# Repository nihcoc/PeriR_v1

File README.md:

# PeriR

A custom Software Defined Radio (SDR) carrier board built around the **Xilinx Zynq-7020 SoC** and **Analog Devices AD9364** RF transceiver. The board is designed to run **Kuiper Linux** (Analog Devices' Raspberry Pi OS-based distro) out of the box, with native support for GNU Radio and SDR++ applications.

---

## Overview

This project is inspired by the [FreeSRP](http://electronics.kitchen/misc/freesrp/) open-source SDR by Lukas Lao Beyer and borrows design references from the **FMCOMMS4**, **Zedboard**, **ADRV9364-Z7020**, and **PlutoSDR**.

The goal is a powerful, Linux-capable SDR transceiver with a compact form factor and eventually, a handheld device like the HackRF Portapack.

---

## Key Specifications

| Feature | Detail |
|---|---|
| **SoC / FPGA** | Xilinx Zynq-7020 (ARM Cortex-A9, ~85K LUTs) |
| **RF Transceiver** | Analog Devices AD9364 |
| **Frequency Range** | 70 MHz – 6.0 GHz |
| **Bandwidth** | 200 kHz – 56 MHz |
| **RAM** | 2× 128MB DDR3 (256MB total, Zedboard config) |
| **OS** | Kuiper Linux (Analog Devices / Raspberry Pi OS based) |
| **Primary Storage** | MicroSD card |

---

## Block Diagram

```
Antenna
   │
   ▼
AD9364 RF Transceiver (70MHz–6GHz)
   │  LVDS (max throughput)
   ▼
Zynq-7020 (PS + PL)
   ├── ARM Cortex-A9 (PS) ──► DDR3 RAM, SD Card, USB-OTG, Ethernet, HDMI
```

---

## Hardware Design

### RF Transceiver — AD9364
- **Signalling standard:** LVDS (chosen over CMOS for lower EMI and higher throughput)
- **Interface:** Connected to FPGA Bank 34 (VCCO = 2.5V, `LVDS_25` standard)
- **Balun:** TCM1-63AX+ wideband RF transformer (≤1.8 dB insertion loss @ 6 GHz)
- **Clock:** 40 MHz, 10 pF load capacitance (tested reference from AD)
- **Power rail:** 1.3V via ADP1754ACPZ-1.3-R7 (AD-recommended for stability)
- **TX Power Amp:** PGA-102 (dedicated clean 3.3V supply)

### Zynq-7020 SoC
- **PS Clock:** 33.33 MHz  
- **PL Clock:** 100 MHz (EPSON SG-8018CA oscillator)
- **Boot:** SD Card (primary), QSPI Flash (fallback)
- **Configuration:** Boot mode selectable via header pins/switches
- **RAM interface:** Signal lines terminated at 40 Ω

### Power Architecture

Power sequencing follows **DS187** requirements:
1. VCCPINT (1.0V)
2. VCCPAUX + VCCPLL (1.8V) — simultaneously
3. PS VCCO supplies: VCCOMIO0, VCCOMIO1, VCCO_DDR (3.3V / 1.5V / 0.75V)

| Rail | IC | Current | Usage |
|---|---|---|---|
| 1.0V | TPS62130A | 3A | Zynq VCCINT, VCCBRAM |
| 1.8V | TPS62130A | 3A | Zynq VCCAUX, VCCADC, MIO logic |
| 3.3V | TPS65251-3RHAR (Ch1) | 3A | I/O, SD card, interfaces |
| 2.5V | TPS65251-3RHAR (Ch2) | 2A | FPGA Bank 34 (LVDS) |
| 1.5V | TPS65251-3RHAR (Ch3) | 2A | DDR3 VCCIO |
| 0.75V | MAX1510ETB+ | — | DDR3 VTT termination |
| 1.3V | ADP1754ACPZ-1.3-R7 | — | AD9364 primary supply |
| 5V | External connector | — | Board input power |

> Sequencing is managed using EN (Enable) and PG (Power Good) pins chained between power ICs.
> AD7291BCPZ added for full-board power monitoring.

### Interfaces

| Interface | IC / Notes |
|---|---|
| **HDMI** | ADV7511 transmitter — follows Zedboard design for Kuiper Linux compatibility |
| **USB-OTG** | Standard USB 2.0 OTG with ESD protection |
| **Ethernet** | GbE — backup interface for setup and testing |
| **SD Card** | Level-shifted (1.8V MIO → 3.3V SD logic) |
| **QSPI Flash** | MT25QU128ABA — 128Mb, all data lines active |

## Software

- **OS:** [Kuiper Linux](https://wiki.analog.com/resources/tools-software/linux-software/kuiper-linux) by Analog Devices
- **SDR Applications:** GNU Radio, SDR++
- **FPGA toolchain:** Xilinx Vivado + Analog Devices HDL reference designs
- **Reference HDL:** [Analog Devices HDL](https://github.com/analogdevicesinc/hdl) (FMCOMMS4 / ADRV9364 compatible)

---

## Design References

- [FreeSRP](http://electronics.kitchen/misc/freesrp/) — Lukas Lao Beyer
- Analog Devices FMCOMMS4
- Xilinx Zedboard
- ADRV9364-Z7020
- PlutoSDR
- **Key Datasheets:** UG585, UG933, UG482, UG470, UG483, DS187, AD9364 Reference Manual

---

## Project Status

- [x] Component selection
- [x] Schematic capture
- [x] Footprint assignment
- [x] Schematic verification (round 1)
- [ ] Schematic verification (round 2)
- [ ] PCB layout & routing
- [ ] DFM review
- [ ] Fabrication & assembly
- [ ] Bring-up & firmware development
- [ ] HAT board design

---

*This is a personal learning project. Feedback and suggestions welcome — especially on the RF and LVDS sections!*

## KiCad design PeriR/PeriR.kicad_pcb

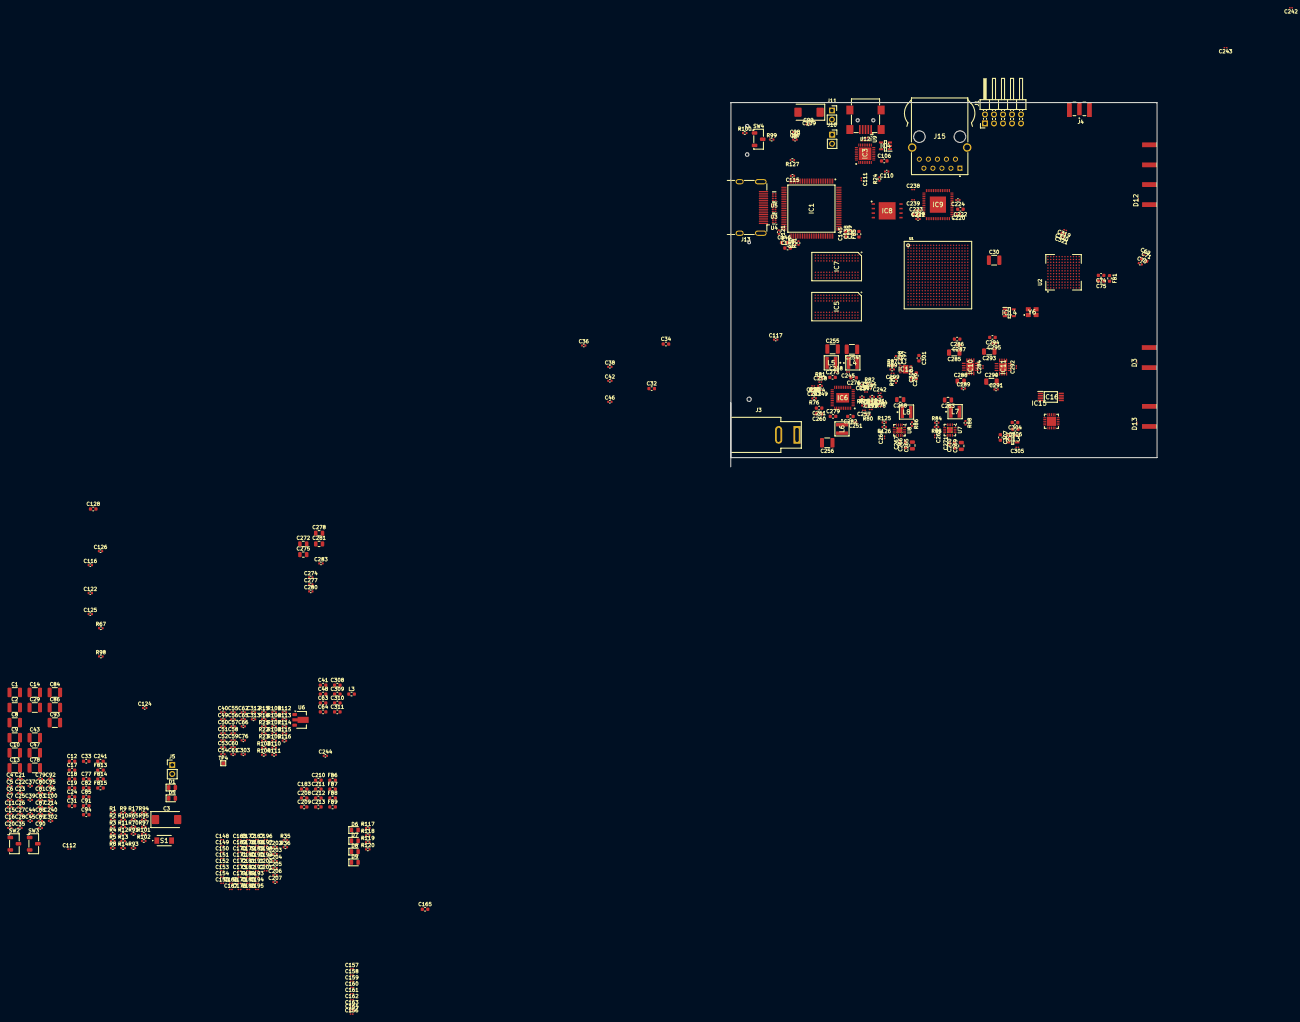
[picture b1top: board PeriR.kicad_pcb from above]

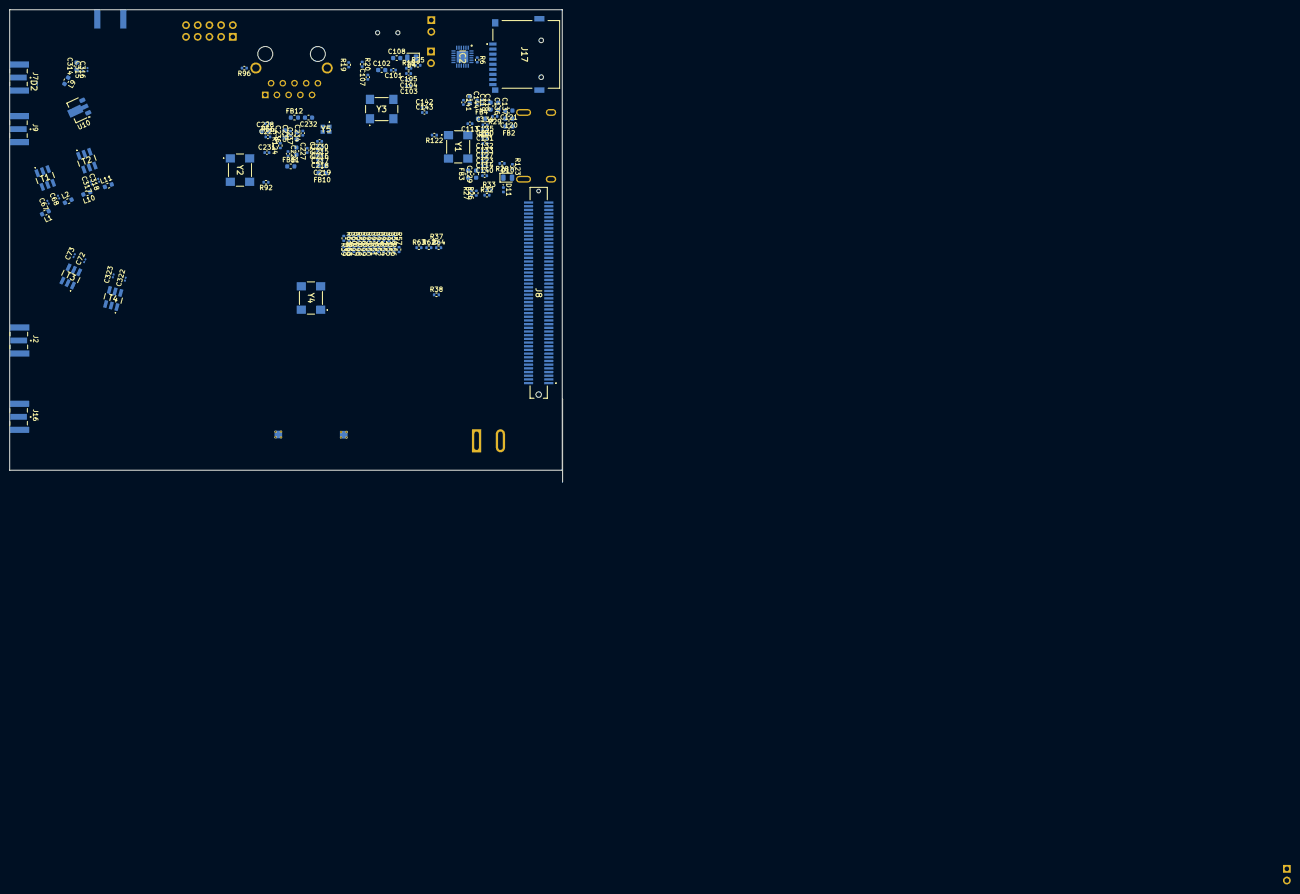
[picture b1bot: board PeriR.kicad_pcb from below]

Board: 6 copper layers, 120.1 x 102.6 mm, 546 parts (135 on the bottom side), 420 nets, no tracks yet.

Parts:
C1, C2: 4.7uF; C_1210_3225Metric
C3: 330uF; CP_EIA-7343-31_Kemet-D
C4, C5, C6, C7, C11, C15, C16, C20, C21, C22, C23, C25, C26, C27, C28, C35, C36, C37, C38, C39, C42, C45, C46, C79, C80, C81, C83, C87, C88, C89, C90, C92, C95, C240, C302: 0.47uF; C_0402_1005Metric
C8, C9, C13, C29, C30, C47, C78, C84, C86, C93: 100uF; C_1210_3225Metric
C10, C14, C43: 47uF; C_1210_3225Metric
C12, C17, C18, C19, C24, C31, C32, C33, C34, C77, C82, C85, C91, C94, C108, C165, C183, C219, C222, C228, C232, C237, C308: 4.7uF; C_0603_1608Metric
C40, C44, C49, C50, C51, C52, C53, C54, C55, C56, C57, C58, C59, C60, C61, C62, C65, C66, C96, C97, C98, C99, C100, C101, C103, C104, C105, C107, C110, C113, C114, C115, C116, C117, C118, C119, C122, C123, C124, C125, C126, C127, C130, C131, C132, C133, C134, C135, C138, C139, C140, C141, C142, C143, C202, C203, C204, C205, C206, C207, C214, C215, C216, C217, C218, C220, C221, C224, C225, C226, C229, C230, C231, C233, C234, C235, C303, C312, C313: 0.1uF; C_0402_1005Metric
C41, C48, C120, C128, C136, C144, C146, C147, C210, C211, C223, C227, C236, C300, C304, C306, C307, C309, C314: 1uF; C_0603_1608Metric
C63, C64, C71, C74, C75, C121, C129, C137, C145, C261, C266, C270, C273, C276, C279, C282, C286, C294, C301, C310, C311: 10uF; C_0603_1608Metric
C67, C68, C72, C73, C317, C318, C322, C323: 18pF; C_0201_0603Metric
C69, C299, C319: 1nF; C_0201_0603Metric
C70, C267, C271, C274, C277, C280, C283, C287, C289, C291, C295, C297, C320: 100nF; C_0402_1005Metric
C76: 0.1uF (DNP); C_0402_1005Metric
C102, C106: 22uF; C_0603_1608Metric
C109: 150uF; CP_EIA-7343-31_Kemet-D
C111: 15pF; C_0201_0603Metric
C112, C184, C185, C186, C187, C196, C197, C198, C199, C200, C201, C284, C292, C305: 10nF; C_0201_0603Metric
C148, C149, C150, C151, C152, C153, C154, C155, C156, C157, C158, C159, C160, C161, C162, C163, C166, C167, C168, C169, C170, C171, C172, C173, C174, C175, C176, C177, C178, C179, C180, C181, C188, C189, C190, C191, C192, C193, C194, C195, C245, C248, C251: 47nF; C_0201_0603Metric
C164: 470nF; C_0402_1005Metric
C182: 470nF; C_0201_0603Metric
C208, C209: 10nF; C_0603_1608Metric
C212, C213: 2.2uF; C_0603_1608Metric
C238, C239: 39pF; C_0201_0603Metric
C241: 10uF(0603); C_0603_1608Metric
C242, C316: 68pF; C_0201_0603Metric
C242#2, C243, C244#2, C246, C250, C253, C257, C258, C259: 4.7nF; C_0201_0603Metric
C243#2, C315: 1.2nF; C_0201_0603Metric
C244: 1uF; C_0402_1005Metric
C247, C249, C252: 100pF; C_0201_0603Metric
C254, C255, C256: 22uF; C_1210_3225Metric
C260: 3.3uF; C_0603_1608Metric
C262, C264: 2.2nF; C_0201_0603Metric
C263, C268: 22uF; C_0805_2012Metric
C265, C269, C272, C275, C278, C281, C288: 47uF; C_0805_2012Metric
C285, C290, C293: 47uF; C_1206_3216Metric
C296: 100uF; C_0402_1005Metric
C298: 0.33uF; C_0402_1005Metric
C321: 10uF; C_0201_0603Metric
D1, D6, D7, D8, D9: LED; LED_0805_2012Metric
D2, D3, D12, D13: ESD8472MUT5G; X3DFN2-CASE152AF-ISSUE-A
D4: D; D_0805_2012Metric
D5, D10: D_Schottky; D_0805_2012Metric
D11: PESD0402-140; D_0402_1005Metric
FB1, FB2, FB3, FB4, FB5, FB6, FB7, FB8, FB9: BLM21AG601SN1D; L_0603_1608Metric
FB10, FB11, FB12: MPZ1608S101ATAH0; L_0603_1608Metric
FB13: BLM18SG121TN1D; L_0603_1608Metric
FB14, FB15: BLM18SG221TN1D; L_0603_1608Metric
IC1: ADV7511KSTZ; QFP50P1600X1600X160-100N
IC2: TXS02612RTWR; QFN50P400X400X80-25N-D
IC3: TUSB1210BRHB; QFN50P500X500X100-33N-D
IC4: TPS2051BDBVTG4; SOT95P280X145-5N
IC5, IC7: MT41K128M16JT-125 :K; BGA96C80P9X16_800X1400X120
IC6: TPS65251-3RHAR; QFN50P600X600X100-41N-D
IC8: S25FL256SAGNFI001; SON127P800X600X80-9N-D
IC9: 88E1512-XX-NNP2I000; QFN50P800X800X100-57N-D
IC10, IC11: ADP1754ACPZ-1.3-R7; QFN65P400X400X80-17N-D
IC12: MAX1510ETB+; SON50P300X300X80-11N
IC13: NCP700BSN33T1G; SOT95P275X110-5N
IC14: ADM7160AUJZ-1.8-R7; SOT95P280X100-5N
IC15: AD7291BCPZ; QFN50P400X400X80-21N
IC16: M24C02-WDW6TP; SOP65P640X120-8N
J1: Conn_02x05_Top_Bottom; PinHeader_2x05_P2.54mm_Horizontal
J2, J4, J7, J9, J16: SMA-J-P-H-ST-EM1; SAMTEC_SMA-J-P-H-ST-EM1
J3: Barrel_Jack; BarrelJack_SwitchcraftConxall_RAPC10U_Horizontal
J5: Conn_01x02_Pin; PinHeader_1x02_P2.54mm_Vertical
J8: 61082-101400LF; 61082101400LF
J10, J11: Conn_01x02_Pin; PinSocket_1x02_P2.54mm_Vertical
J12: USB_B_Mini; USB_Mini-B_Wuerth_65100516121_Horizontal
J13: HDMI_A_1.4; HDMI_A_Molex_208658-1001_Horizontal
J15: HFJ11-1G02ERL; HFJ111G02ERL
J17: MICRO-SD-CARD; MICROSDCARD
L1, L2, L10, L11: 330LH; L_0603_1608Metric
L3, L9: 43nH; L_0603_1608Metric
L4: 1uH; XFL4020-222ME
L5, L6: 1.5uH; XFL4020-222ME
L7, L8: 2.2uH; XFL4020-222ME
R1, R3, R6, R24, R64, R122, R124: 4.7K; R_0402_1005Metric
R2: 270R; R_0402_1005Metric
R4, R15, R34, R87, R89, R90, R102, R103, R105, R107, R109, R111, R113, R115: 10K; R_0402_1005Metric
R5, R7, R17: 4.7K(0R); R_0402_1005Metric
R8, R9, R10, R11, R12, R13, R14, R73, R74, R77: 20K; R_0402_1005Metric
R16: 14.3K 1%; R_0402_1005Metric
R18, R26, R27, R28, R30, R31: 2K; R_0402_1005Metric
R19, R20, R86, R88: 100K; R_0402_1005Metric
R21, R22: 1R; R_0402_1005Metric
R23, R67, R97: 49.9R; R_0402_1005Metric
R25, R66, R96: 0R; R_0402_1005Metric
R29: 887R; R_0402_1005Metric
R32, R33: 50R; R_0402_1005Metric
R35, R36, R62: 80R; R_0402_1005Metric
R37, R38: 240R; R_0402_1005Metric
R39, R40, R41, R42, R43, R44, R45, R46, R47, R48, R49, R50, R51, R52, R53, R54, R55, R56, R57, R58, R59, R60, R61, R63: 40R; R_0402_1005Metric
R65, R117, R118, R119, R120: 330R; R_0402_1005Metric
R70: 100k; R_0402_1005Metric
R71, R75, R78: 40.2K; R_0402_1005Metric
R72: 12.8K; R_0402_1005Metric
R76: 45.9K; R_0402_1005Metric
R79: 18.9K; R_0402_1005Metric
R80, R81: 137K; R_0402_1005Metric
R82: 86.6K; R_0402_1005Metric
R83: 135.4K; R_0402_1005Metric
R84: 51K; R_0402_1005Metric
R85, R125: 200K; R_0402_1005Metric
R91, R92: 24R; R_0402_1005Metric
R93, R94, R95: 10k; R_0402_1005Metric
R98, R127: 499R; R_0402_1005Metric
R99, R100: 50K; R_0402_1005Metric
R101: 1K; R_0402_1005Metric
R104, R106, R108, R110, R112, R114, R116: 16K; R_0402_1005Metric
R121: 50; R_0402_1005Metric
R123: 27K; R_0402_1005Metric
R126: 160K; R_0402_1005Metric
S1: TS-1088-AR02016; TS1088AR02016
SW2, SW3, SW4: SW_Nidec_CAS-120A1; Nidec_Copal_CAS-120A
T1, T2, T3, T4: TCM1-63AX_; TCM163AX
TP4: TestPoint; TestPoint_Pad_1.0x1.0mm
U1: XC7Z020CLG484; CS484
U2: AD9364BBCZ; BGA144C80P12X12_1000X1000X170N
U3, U4, U5, U9: TPD4E05U06DQA; USON-10_2.5x1.0mm_P0.5mm
U6, U10: PGA-102; SOT-89-3
U7, U8: TPS62130A; VQFN-16-1EP_3x3mm_P0.5mm_EP1.68x1.68mm_ThermalVias
Y1: XL2EL89COI-111YLC-12M; SG8018CA1000000MTJHSA0
Y2: OT3EL89CJI-111YLC-33.33M; SG8018CA1000000MTJHSA0
Y3: XL2EL89COI-111YLC-26M; SG8018CA1000000MTJHSA0
Y4: SG-8018CA_100.0000M-TJHSA0; SG8018CA1000000MTJHSA0
Y5: NX2016SA-25MHZ-STD-CZS-2; FA128400000MF20XK
Y6: ECS-TXO-32CSMV-400-BN-TR; ECSTXO32CSMV400BNTR

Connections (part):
0V75: C202.1, C203.1, C204.1, C205.1, C206.1, C207.1, C208.1, C209.1, C210.1, C211.1, C212.1, C213.1, C296.1, IC12.6 (OUTS), IC12.9 (OUT), R39.2, R40.2, R41.2, R42.2, R43.2, R44.2, R45.2, R46.2, R47.2, R48.2, R49.2, R50.2, R51.2, R52.2, R53.2, R54.2, R55.2, R56.2, R57.2, R58.2, R59.2, R60.2, R61.2, R63.1
1V0_PG: R88.2, U7.4 (PG), U7.7 (FSW), U8.13 (EN)
1V3_PG: IC10.5 (PG), IC11.5 (PG)
1V8_PG: IC6.11 (EN1), IC6.20 (EN2), IC6.40 (EN3), R86.2, U8.4 (PG), U8.7 (FSW)
+1V0: C1.1, C2.1, C3.1, C4.1, C5.1, C6.1, C7.1, C8.1, C10.1, C11.1, C47.1, C77.1, C79.1, C80.1, C81.1, C263.1, L7.2, R84.1, R88.1, R111.1, U1.G8 (VCCPINT@0), U1.H9 (VCCPINT@1), U1.H11 (VCCBRAM@0), U1.J8 (VCCPINT@2), U1.J10 (VCCBRAM@1), U1.J12 (VCCINT@0), U1.J14 (VCCINT@1), U1.K13 (VCCINT@2), U1.L8 (VCCPINT@3), U1.L14 (VCCINT@3), U1.M13 (VCCINT@4), U1.N8 (VCCPINT@4), U1.N14 (VCCINT@5), U1.P13 (VCCINT@6), U1.R8 (VCCPINT@5), U1.R14 (VCCINT@7), U7.14 (VOS)
+1V3: C49.1, C50.1, C51.1, C52.1, C53.1, C54.1, C55.1, C56.1, C57.1, C75.1, C293.1, C294.1, C295.1, FB1.2, IC11.9 (SENSE), IC11.10 (VOUT_1), IC11.11 (VOUT_2), IC11.12 (VOUT_3), IC11.13 (VOUT_4), IC11.14 (VOUT_5), R109.1, U2.A7 (VDDA1P3_RX_TX), U2.A8 (VDDA1P3_RX_TX), U2.A9 (VDDA1P3_RX_TX), U2.A10 (VDDA1P3_RX_TX), U2.D2 (VDDA1P3_RX_RF), U2.D3 (VDDA1P3_RX_TX), U2.E3 (VDDA1P3_TX_LO_BUFFER), U2.F12 (VDDD1P3_DIG), U2.K4 (VDDA1P3_BB)
+1V3SYNTH: C58.1, C59.1, C60.1, C61.1, C62.1, C63.1, C64.1, C285.1, C286.1, C287.1, IC10.9 (SENSE), IC10.10 (VOUT_1), IC10.11 (VOUT_2), IC10.12 (VOUT_3), IC10.13 (VOUT_4), IC10.14 (VOUT_5), U2.B9 (VDDA1P3_TX_LO), U2.B10 (VDDA1P3_TX_VCO_LDO), U2.E2 (VDDA1P3_RX_LO), U2.F2 (VDDA1P3_RX_VCO_LDO), U2.J3 (VDDA1P3_RX_SYNTH), U2.K3 (VDDA1P3_TX_SYNTH)
+1V3_TX: C69.1, C70.1, C71.1, C74.1, C319.1, C320.1, C321.1, FB1.1, L1.2, L2.2, L10.2, L11.2
+1V5: C84.1, C85.1, C87.1, C88.1, C89.1, C90.1, C148.1, C149.1, C150.1, C151.1, C152.1, C153.1, C154.1, C155.1, C156.1, C157.1, C158.1, C159.1, C160.1, C161.1, C162.1, C163.1, C164.1, C165.1, C166.1, C167.1, C168.1, C169.1, C170.1, C171.1, C172.1, C173.1, C174.1, C175.1, C176.1, C177.1, C178.1, C179.1, C180.1, C181.1, C182.1, C183.1, C184.1, C188.1, C189.1, C190.1, C191.1, C192.1, C193.1, C194.1, C195.1, C196.1, C197.1, C198.1, C199.1, C200.1, C202.2, C203.2, C204.2, C205.2, C206.2, C207.2, C208.2, C209.2, C210.2, C211.2, C212.2, C213.2, C243.2, C255.1, FB6.1, FB6.2, FB7.1, FB7.2, FB8.1, FB8.2, FB9.1, FB9.2, IC5.A1 (VDDQ_1), IC5.A8 (VDDQ_2)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
+1V8: C12.1, C14.1, C15.1, C16.1, C44.1, C78.1, C82.1, C83.1, C93.1, C94.1, C95.1, C99.2, C103.2, C104.2, C105.2, C268.1, C288.2, C289.2, C290.2, C291.2, FB2.1, FB4.1, FB5.1, FB11.1, FB13.1, FB14.2, IC2.5 (VCCA), IC3.11 (CS), IC3.14 (CFG), IC3.28 (VDD18_1), IC3.30 (VDD18_2), IC3.32 (VDDIO), IC10.1 (VIN_1), IC10.2 (VIN_2), IC10.3 (VIN_3), IC10.4 (EN), IC10.15 (VIN_4), IC10.16 (VIN_5), IC11.1 (VIN_1), IC11.2 (VIN_2), IC11.3 (VIN_3), IC11.4 (EN), IC11.15 (VIN_4), IC11.16 (VIN_5), J8.91, J8.93, J8.95, J8.97, J8.99, L8.2, R18.2, R70.2, R86.1, R93.2, R94.2, R99.2, R113.1, R124.1, R125.1, U1.A10 (VCCO_MIO1_501@0), U1.B13 (VCCO_MIO1_501@1), U1.D9 (VCCO_MIO1_501@2), U1.E12 (VCCO_MIO1_501@3), U1.G9 (VCCBATT_0), U1.K9 (VCCPAUX@0), U1.L10 (VCCAUX@0), U1.M9 (VCCPAUX@1), U1.N10 (VCCAUX@1), U1.P9 (VCCPAUX@2), U1.P11 (VCCAUX@2), U1.R10 (VCCAUX@3), U1.T9 (VCCPAUX@3), U8.14 (VOS)
+2V5: C9.1, C13.1, C17.1, C18.1, C19.1, C20.1, C21.1, C22.1, C23.1, C24.1, C25.1, C26.1, C27.1, C28.1, C66.1, C244#2.2, C256.1, L6.2, R15.1, R19.1, R78.1, R102.2, R115.1, U1.A20 (VCCO_35@0), U1.C16 (VCCO_35@1), U1.D19 (VCCO_35@2), U1.E22 (VCCO_35@3), U1.F15 (VCCO_35@4), U1.G18 (VCCO_35@5), U1.H21 (VCCO_35@6), U1.K17 (VCCO_34@0), U1.L20 (VCCO_34@1), U1.N16 (VCCO_34@2), U1.P19 (VCCO_34@3), U1.R22 (VCCO_34@4), U1.T15 (VCCO_34@5), U2.H12 (VDD_INTERFACE)
+3V3: C29.1, C30.1, C31.1, C32.1, C33.1, C34.1, C35.1, C36.1, C37.1, C38.1, C39.1, C42.1, C43.1, C45.1, C46.1, C65.1, C86.1, C91.1, C92.1, C96.1, C97.2, C98.2, C100.1, C101.2, C102.2, C110.2, C113.2, C214.2, C242#2.2, C254.1, C300.2, C301.2, C311.2, C312.2, C313.2, FB3.1, FB10.1, FB12.1, IC2.21 (VCCB0), IC3.20 (VDD33), IC8.8 (VCC), IC12.2 (VCC), IC12.7 (~SHDN), IC12.10 (IN), IC14.1 (VIN), IC14.3 (EN), IC15.10 (VDD), IC15.16 (VDRIVE), IC15.17 (~PD/~RST), IC16.8 (VCC), J1.2, J8.41, J8.43, J8.45, J8.47, J8.49, J15.9 (VCC), J17.4 (VDD), L4.2, R1.1, R2.1, R3.1, R4.2, R5.1, R6.1, R14.2, R17.1, R24.2, R26.1, R27.1, R28.1, R65.1, R71.1, R90.1, R103.1, R122.2, R123.1, SW2.3 (A), SW3.3 (A), U1.AA10 (VCCO_13@5)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
+3V3_TX: C242.1, C243#2.1, C244.1, C304.1, C306.1, C314.1, C315.1, C316.1, IC13.5 (OUT), L3.1, L9.1
+5V: C107.2, C265.2, C266.2, C267.2, C269.2, C270.2, C271.2, C272.1, C273.2, C274.2, C275.1, C276.2, C277.2, C278.1, C279.2, C280.2, C281.1, C282.2, C283.2, C307.1, IC4.5 (IN), IC6.13 (VIN1), IC6.18 (VIN2), IC6.32 (VIN_1), IC6.33 (VIN_2), IC6.34 (VIN_3), IC6.38 (VIN3), IC13.1 (IN), IC13.3 (EN), J3.1, J8.17, J8.19, J8.21, J8.23, J8.25, J8.27, J8.29, J8.31, J8.33, J8.35, J8.37, J8.39, J13.18 (+5V), R30.1, R31.1, U7.10 (VIN), U7.11 (VIN), U7.12 (VIN), U7.13 (EN), U8.10 (VIN), U8.11 (VIN), U8.12 (VIN)
/DDR/A0: IC5.N3 (A0), IC7.N3 (A0), R39.1, U1.M4 (PS_DDR_A0_502)
/DDR/A1: IC5.P7 (A1), IC7.P7 (A1), R40.1, U1.M5 (PS_DDR_A1_502)
/DDR/A2: IC5.P3 (A2), IC7.P3 (A2), R41.1, U1.K4 (PS_DDR_A2_502)
/DDR/A3: IC5.N2 (A3), IC7.N2 (A3), R42.1, U1.L4 (PS_DDR_A3_502)
/DDR/A4: IC5.P8 (A4), IC7.P8 (A4), R43.1, U1.K6 (PS_DDR_A4_502)
/DDR/A5: IC5.P2 (A5), IC7.P2 (A5), R44.1, U1.K5 (PS_DDR_A5_502)
/DDR/A6: IC5.R8 (A6), IC7.R8 (A6), R45.1, U1.J7 (PS_DDR_A6_502)
/DDR/A7: IC5.R2 (A7), IC7.R2 (A7), R46.1, U1.J6 (PS_DDR_A7_502)
/DDR/A8: IC5.T8 (A8), IC7.T8 (A8), R47.1, U1.J5 (PS_DDR_A8_502)
/DDR/A9: IC5.R3 (A9), IC7.R3 (A9), R48.1, U1.H5 (PS_DDR_A9_502)
/DDR/A10: IC5.L7 (A10/AP), IC7.L7 (A10/AP), R49.1, U1.J3 (PS_DDR_A10_502)
/DDR/A11: IC5.R7 (A11), IC7.R7 (A11), R50.1, U1.G5 (PS_DDR_A11_502)
/DDR/A12: IC5.N7 (A12/BC#), IC7.N7 (A12/BC#), R51.1, U1.H4 (PS_DDR_A12_502)
/DDR/A13: IC5.T3 (A13), IC7.T3 (A13), R52.1, U1.F4 (PS_DDR_A13_502)
/DDR/A14: IC5.T7 (A14), IC7.T7 (A14), R53.1, U1.G4 (PS_DDR_A14_502)
/DDR/BA0: IC5.N8 (BA1), IC7.N8 (BA1), R54.1, U1.L7 (PS_DDR_BA0_502)
/DDR/BA1: IC5.M3 (BA2), IC7.M3 (BA2), R55.1, U1.L6 (PS_DDR_BA1_502)
/DDR/BA2: IC5.M2 (BA0), IC7.M2 (BA0), R56.1, U1.M6 (PS_DDR_BA2_502)
/DDR/CAS: IC5.K3 (CAS#), IC7.K3 (CAS#), R57.1, U1.P3 (PS_DDR_CAS_B_502)
/DDR/CKE: IC5.K9 (CKE), IC7.K9 (CKE), R63.2, U1.V3 (PS_DDR_CKE_502)
/DDR/CKN: IC5.K7 (CK#), IC7.K7 (CK#), R62.2, U1.N5 (PS_DDR_CKN_502)
/DDR/CKP: IC5.J7 (CK), IC7.J7 (CK), R62.1, U1.N4 (PS_DDR_CKP_502)
/DDR/CS: IC5.L2 (CS#), IC7.L2 (CS#), R60.1, U1.P6 (PS_DDR_CS_B_502)
/DDR/DM0: IC7.E7 (LDM), U1.B1 (PS_DDR_DM0_502)
/DDR/DM1: IC7.D3 (UDM), U1.H3 (PS_DDR_DM1_502)
/DDR/DM2: IC5.E7 (LDM), U1.P1 (PS_DDR_DM2_502)
/DDR/DM3: IC5.D3 (UDM), U1.AA2 (PS_DDR_DM3_502)
/DDR/DQ0: IC7.E3 (DQ0), U1.D1 (PS_DDR_DQ0_502)
/DDR/DQ1: IC7.F7 (DQ1), U1.C3 (PS_DDR_DQ1_502)
/DDR/DQ2: IC7.F2 (DQ2), U1.B2 (PS_DDR_DQ2_502)
/DDR/DQ3: IC7.F8 (DQ3), U1.D3 (PS_DDR_DQ3_502)
/DDR/DQ4: IC7.H3 (DQ4), U1.E3 (PS_DDR_DQ4_502)
/DDR/DQ5: IC7.H8 (DQ5), U1.E1 (PS_DDR_DQ5_502)
/DDR/DQ6: IC7.G2 (DQ6), U1.F2 (PS_DDR_DQ6_502)
/DDR/DQ7: IC7.H7 (DQ7), U1.F1 (PS_DDR_DQ7_502)
/DDR/DQ8: IC7.D7 (DQ8), U1.G2 (PS_DDR_DQ8_502)
/DDR/DQ9: IC7.C3 (DQ9), U1.G1 (PS_DDR_DQ9_502)
/DDR/DQ10: IC7.C8 (DQ10), U1.L1 (PS_DDR_DQ10_502)
/DDR/DQ11: IC7.C2 (DQ11), U1.L2 (PS_DDR_DQ11_502)
/DDR/DQ12: IC7.A7 (DQ12), U1.L3 (PS_DDR_DQ12_502)
/DDR/DQ13: IC7.A2 (DQ13), U1.K1 (PS_DDR_DQ13_502)
/DDR/DQ14: IC7.B8 (DQ14), U1.J1 (PS_DDR_DQ14_502)
/DDR/DQ15: IC7.A3 (DQ15), U1.K3 (PS_DDR_DQ15_502)
/DDR/DQ16: IC5.E3 (DQ0), U1.M1 (PS_DDR_DQ16_502)
/DDR/DQ17: IC5.F7 (DQ1), U1.T3 (PS_DDR_DQ17_502)
/DDR/DQ18: IC5.F2 (DQ2), U1.N3 (PS_DDR_DQ18_502)
/DDR/DQ19: IC5.F8 (DQ3), U1.T1 (PS_DDR_DQ19_502)
/DDR/DQ20: IC5.H3 (DQ4), U1.R3 (PS_DDR_DQ20_502)
/DDR/DQ21: IC5.H8 (DQ5), U1.T2 (PS_DDR_DQ21_502)
/DDR/DQ22: IC5.G2 (DQ6), U1.M2 (PS_DDR_DQ22_502)
/DDR/DQ23: IC5.H7 (DQ7), U1.R1 (PS_DDR_DQ23_502)
/DDR/DQ24: IC5.D7 (DQ8), U1.AA3 (PS_DDR_DQ24_502)
/DDR/DQ25: IC5.C3 (DQ9), U1.U1 (PS_DDR_DQ25_502)
/DDR/DQ26: IC5.C8 (DQ10), U1.AA1 (PS_DDR_DQ26_502)
/DDR/DQ27: IC5.C2 (DQ11), U1.U2 (PS_DDR_DQ27_502)
/DDR/DQ28: IC5.A7 (DQ12), U1.W1 (PS_DDR_DQ28_502)
/DDR/DQ29: IC5.A2 (DQ13), U1.Y3 (PS_DDR_DQ29_502)
/DDR/DQ30: IC5.B8 (DQ14), U1.W3 (PS_DDR_DQ30_502)
/DDR/DQ31: IC5.A3 (DQ15), U1.Y1 (PS_DDR_DQ31_502)
/DDR/DQS0_N: IC7.G3 (LDQS#), U1.D2 (PS_DDR_DQS_N0_502)
/DDR/DQS0_P: IC7.F3 (LDQS), U1.C2 (PS_DDR_DQS_P0_502)
/DDR/DQS1_N: IC7.B7 (UDQS#), U1.J2 (PS_DDR_DQS_N1_502)
/DDR/DQS1_P: IC7.C7 (UDQS), U1.H2 (PS_DDR_DQS_P1_502)
/DDR/DQS2_N: IC5.G3 (LDQS#), U1.P2 (PS_DDR_DQS_N2_502)
/DDR/DQS2_P: IC5.F3 (LDQS), U1.N2 (PS_DDR_DQS_P2_502)
/DDR/DQS3_N: IC5.B7 (UDQS#), U1.W2 (PS_DDR_DQS_N3_502)
/DDR/DQS3_P: IC5.C7 (UDQS), U1.V2 (PS_DDR_DQS_P3_502)
/DDR/ODT: IC5.K1 (ODT), IC7.K1 (ODT), R61.1, U1.P5 (PS_DDR_ODT_502)
/DDR/RAS: IC5.J3 (RAS#), IC7.J3 (RAS#), R58.1, U1.R5 (PS_DDR_RAS_B_502)
/DDR/RESET: IC5.T2 (RESET#), IC7.T2 (RESET#), R64.1, U1.F3 (PS_DDR_DRST_B_502)
/DDR/VRN: R35.2, U1.M7 (PS_DDR_VRN_502)
/DDR/VRP: R36.1, U1.N7 (PS_DDR_VRP_502)
/DDR/WE: IC5.L3 (WE#), IC7.L3 (WE#), R59.1, U1.R4 (PS_DDR_WE_B_502)
/FPGA/BMODE0(5): IC8.7 (HOLD#/IO3), R10.1, U1.A3 (PS_MIO5_500)
/FPGA/BMODE1(3): IC8.2 (SO/IO1), R8.1, U1.F6 (PS_MIO3_500)
/FPGA/BMODE2(4): IC8.3 (WP#/IO2), R9.1, U1.E4 (PS_MIO4_500)
/FPGA/BMODE3(2): IC8.5 (SI/IO0), R11.1, U1.A2 (PS_MIO2_500)
/FPGA/DONE: D1.2 (A), R2.2, U1.T12 (DONE_0)
/FPGA/INIT_B: R1.2, U1.T14 (INIT_B_0)
/FPGA/PLLMODE(6): R12.1, R91.2, U1.A4 (PS_MIO6_500)
/FPGA/PL_CLK: U1.Y9 (IO_L12P_T1_MRCC_13), Y4.3 (OUT)
/FPGA/PRGM_B: R3.2, U1.T11 (PROGRAM_B_0)
/FPGA/PS_CLK: R92.2, U1.F7 (PS_CLK_500)
/FPGA/SPI_S#: IC8.1 (CS#), R65.2, U1.A1 (PS_MIO1_500)
/FPGA/TCK: J1.6, U1.G11 (TCK_0)
/FPGA/TD0: J1.7, U1.G14 (TDO_0)
/FPGA/TDI: J1.10, U1.H13 (TDI_0)
/FPGA/TMS: J1.8, U1.G12 (TMS_0)
/FPGA/VCCPLL: C240.1, C241.1, FB13.2, U1.H10 (VCCPLL)
/FPGA/VMODEB0(7): R13.1, U1.D5 (PS_MIO7_500)
/FPGA/VMODEB1(8): R14.1, U1.E5 (PS_MIO8_500)
/FPGA/VREF_0V9: C112.2, R94.1, R95.2, U1.F8 (PS_MIO_VREF_501)
/FPGA/qSPI_CLK: IC8.6 (SCK), R91.1
/INTERFACES/AVDD: C115.2, C130.2, C131.2, C132.2, C133.2, C134.2, C135.2, C136.2, C137.2, FB4.2, IC1.24 (PVDD_1), IC1.25 (PVDD_2), IC1.29 (AVDD_1), IC1.34 (AVDD_2), IC1.41 (AVDD_3)
/INTERFACES/AVDD_18: C224.2, C229.2, C230.2, C231.2, C232.2, IC9.3 (AVDD18_1), IC9.10 (VDDO_SEL), IC9.19 (AVDD18_2), IC9.26 (AVDD18_3), IC9.35 (AVDDC18), IC9.38 (AVDD18_4), IC9.39 (AVDD18_OUT)
/INTERFACES/AVDD_33: C234.2, C235.2, C236.2, C237.2, FB12.2, IC9.20 (AVDD33_1), IC9.25 (AVDD33_2)
/INTERFACES/CEC_CLK: IC1.50 (CEC_CLK), R121.1
/INTERFACES/CLK: IC2.19 (CLKB0), J17.5 (CLK)
/INTERFACES/CMD: IC2.20 (CMDB0), J17.3 (CMD), R6.2
/INTERFACES/DA0: IC2.18 (DA0B0), J17.7 (DAT0)
/INTERFACES/DA1: IC2.16 (DAT1B0), J17.8 (DAT1)
/INTERFACES/DA2: IC2.23 (DAT2B0), J17.1 (DAT2)
/INTERFACES/DA3: IC2.22 (DAT3B0), J17.2 (CD/DAT3)
/INTERFACES/DVDD: C114.2, C138.2, C139.2, C140.2, C141.2, C142.2, C143.2, C144.2, C145.2, FB5.2, IC1.1 (DVDD_1), IC1.19 (DVDD_2), IC1.49 (DVDD_3), IC1.76 (DVDD_4), IC1.77 (DVDD_5), R32.2, R33.2
/INTERFACES/DVDD_ETH: C220.2, C221.2, C222.2, C223.2, IC9.6 (DVDD_1), IC9.40 (DVDD_OUT), IC9.42 (DVDD_2)
/INTERFACES/HEAC_N: C146.2, IC1.51 (HEAC-), U5.5 (D2-)
/INTERFACES/HEAC_P: C147.2, IC1.52 (HEAC+), U5.1 (D1+)
/INTERFACES/HPD: C146.1, IC1.30 (HPD), J13.19 (HPD/HEAC-), R33.1, R34.1
/INTERFACES/ID: IC3.23 (ID), J12.4 (ID), U9.5 (D2-)
/INTERFACES/MD0N: IC9.27 (MDIN[0]), J15.2 (TD0-)
/INTERFACES/MD0P: IC9.28 (MDIP[0]), J15.1 (TD0+)
/INTERFACES/MD1N: IC9.23 (MDIN[1]), J15.6 (TD1-)
/INTERFACES/MD1P: IC9.24 (MDIP[1]), J15.3 (TD1+)
/INTERFACES/MD2N: IC9.21 (MDIN[2]), J15.5 (TD2-)
/INTERFACES/MD2P: IC9.22 (MDIP[2]), J15.4 (TD2+)
/INTERFACES/MD3N: IC9.17 (MDIN[3]), J15.8 (TD3-)
/INTERFACES/MD3P: IC9.18 (MDIP[3]), J15.7 (TD3+)
/INTERFACES/MVDD: C116.2, C122.2, C123.2, C124.2, C125.2, C126.2, C127.2, C128.2, C129.2, FB3.2, IC1.47 (MVDD)
/INTERFACES/PLVDD: C117.2, C118.2, C119.2, C120.2, C121.2, FB2.2, IC1.21 (PLVDD), IC1.26 (BGVDD)
/INTERFACES/REG_IN: C215.2, C216.2, C217.2, C218.2, C219.2, FB10.2, IC9.36 (REG_IN)
/INTERFACES/VDDO_ETH: C225.2, C226.2, C227.2, C228.2, FB11.2, IC9.11 (VDDO_1), IC9.49 (VDDO_2), IC9.52 (VDDO_3)
/Transceiver/1V0_AD: IC15.4 (VIN6), R111.2, R112.1
/Transceiver/1V3S_AD: IC15.3 (VIN5), R107.2, R108.1
/Transceiver/1V3_AD: IC15.1 (VIN3), R109.2, R110.1
/Transceiver/1V5_AD: IC15.20 (VIN2), R105.2, R106.1
/Transceiver/1V8_AD: IC15.19 (VIN1), R113.2, R114.1
/Transceiver/2V5_AD: IC15.2 (VIN4), R115.2, R116.1
/Transceiver/3V3_AD: IC15.18 (VIN0), R103.2, R104.1
/Transceiver/RX1A_N: C73.1, U2.M2 (RX1A_N)
/Transceiver/RX1A_P: C72.1, U2.M1 (RX1A_P)
/Transceiver/RX1B_N: C323.1, U2.J1 (RX1B_N)
/Transceiver/RX1B_P: C322.1, U2.H1 (RX1B_P)
/Transceiver/TX1A_N: C67.1, C68.1, L1.1, L2.1, U2.M7 (TX1A_P), U2.M8 (TX1A_N)
/Transceiver/TX1B_N: C318.1, L11.1, U2.M10 (TX1B_N)
/Transceiver/TX1B_P: C317.1, L10.1, U2.M9 (TX1B_P)
AD_CI0: U1.A18 (IO_L10P_T1_AD11P_35), U2.C5 (CTRL_IN0)
AD_CI1: U1.A19 (IO_L10N_T1_AD11N_35), U2.C6 (CTRL_IN1)
AD_CI2: U1.D22 (IO_L16P_T2_35), U2.D6 (CTRL_IN2)
AD_CI3: U1.C22 (IO_L16N_T2_35), U2.D5 (CTRL_IN3)
AD_CLK_OUT: U1.L18 (IO_L12P_T1_MRCC_34), U2.J6 (CLK_OUT)
AD_CO0: U1.G20 (IO_L22P_T3_AD7P_35), U2.D4 (CTRL_OUT0)
AD_CO1: U1.G21 (IO_L22N_T3_AD7N_35), U2.E4 (CTRL_OUT1)
AD_CO2: U1.E19 (IO_L21P_T3_DQS_AD14P_35), U2.E5 (CTRL_OUT2)
AD_CO3: U1.E20 (IO_L21N_T3_DQS_AD14N_35), U2.E6 (CTRL_OUT3)
AD_CO4: U1.G19 (IO_L20P_T3_AD6P_35), U2.F6 (CTRL_OUT4)
AD_CO5: U1.F19 (IO_L20N_T3_AD6N_35), U2.F5 (CTRL_OUT5)
AD_CO6: U1.E15 (IO_L3P_T0_DQS_AD1P_35), U2.F4 (CTRL_OUT6)
AD_CO7: U1.D15 (IO_L3N_T0_DQS_AD1N_35), U2.G4 (CTRL_OUT7)
AD_DATA_CLK_N: U1.M20 (IO_L13N_T2_MRCC_34), U2.H11 (DATA_CLK_N)
AD_DATA_CLK_P: U1.M19 (IO_L13P_T2_MRCC_34), U2.G11 (DATA_CLK_P)
AD_ENABLE: U1.J20 (IO_L9P_T1_DQS_34), U2.G6 (ENABLE)
AD_EN_AGC: U1.G15 (IO_L4P_T0_35), U2.G5 (EN_AGC)
AD_FB_CLK_N: U1.J22 (IO_L8N_T1_34), U2.G10 (FB_CLK_N)
AD_FB_CLK_P: U1.J21 (IO_L8P_T1_34), U2.F10 (FB_CLK_P)
AD_RESET: R15.2, U1.A16 (IO_L9P_T1_DQS_AD3P_35), U2.K5 (RESETB)
AD_RX_D0_N: U1.P18 (IO_L20N_T3_34), U2.K11 (P1_D0/RX_D0_N)
AD_RX_D0_P: U1.P17 (IO_L20P_T3_34), U2.J12 (P1_D1/RX_D0_P)
AD_RX_D1_N: U1.P22 (IO_L16N_T2_34), U2.K10 (P1_D2/RX_D1_N)
AD_RX_D1_P: U1.N22 (IO_L16P_T2_34), U2.J11 (P1_D3/RX_D1_P)
AD_RX_D2_N: U1.M22 (IO_L15N_T2_DQS_34), U2.K9 (P1_D4/RX_D2_N)
AD_RX_D2_P: U1.M21 (IO_L15P_T2_DQS_34), U2.J10 (P1_D5/RX_D2_P)
AD_RX_D3_N: U1.K18 (IO_L7N_T1_34), U2.K8 (P1_D6/RX_D3_N)
AD_RX_D3_P: U1.J18 (IO_L7P_T1_34), U2.J9 (P1_D7/RX_D3_P)
AD_RX_D4_N: U1.L22 (IO_L10N_T1_34), U2.K7 (P1_D8/RX_D4_N)
AD_RX_D4_P: U1.L21 (IO_L10P_T1_34), U2.J8 (P1_D9/RX_D4_P)
AD_RX_D5_N: U1.T17 (IO_L21N_T3_DQS_34), U2.J7 (P1_D10/RX_D5_N)
AD_RX_D5_P: U1.T16 (IO_L21P_T3_DQS_34), U2.H8 (P1_D11/RX_D5_P)
AD_RX_FRA_N: U1.N20 (IO_L14N_T2_SRCC_34), U2.G7 (RX_FRAME_N)
AD_RX_FRA_P: U1.N19 (IO_L14P_T2_SRCC_34), U2.G8 (RX_FRAME_P)
AD_SCL: IC15.15 (SCL), IC16.6 (SCL), U1.R7 (IO_0_13)
AD_SDA: IC15.14 (SDA), IC16.5 (SDA), U1.U7 (IO_25_13)
AD_SPI_EN: U1.F18 (IO_L5P_T0_AD9P_35), U2.K6 (SPI_ENB)
AD_SPI_MISO: U1.E21 (IO_L17P_T2_AD5P_35), U2.L6 (SPI_DO)
AD_SPI_MOSI: U1.D21 (IO_L17N_T2_AD5N_35), U2.J4 (SPI_DI)
AD_SPI_SCLK: U1.E18 (IO_L5N_T0_AD9N_35), U2.J5 (SPI_CLK)
AD_SYNC_IN: U1.G16 (IO_L4N_T0_35), U2.H5 (SYNC_IN)
AD_TXNRX: U1.K21 (IO_L9N_T1_DQS_34), U2.H4 (TXNRX)
AD_TX_D0_N: U1.N18 (IO_L5N_T0_34), U2.E12 (P0_D0/TX_D0_N)
AD_TX_D0_P: U1.N17 (IO_L5P_T0_34), U2.D11 (P0_D1/TX_D0_P)
AD_TX_D1_N: U1.P21 (IO_L18N_T2_34), U2.E11 (P0_D2/TX_D1_N)
AD_TX_D1_P: U1.P20 (IO_L18P_T2_34), U2.D10 (P0_D3/TX_D1_P)
AD_TX_D2_N: U1.M17 (IO_L4N_T0_34), U2.E10 (P0_D4/TX_D2_N)
AD_TX_D2_P: U1.L17 (IO_L4P_T0_34), U2.D9 (P0_D5/TX_D2_P)
AD_TX_D3_N: U1.T19 (IO_L22N_T3_34), U2.E9 (P0_D6/TX_D3_N)
AD_TX_D3_P: U1.R19 (IO_L22P_T3_34), U2.D8 (P0_D7/TX_D3_P)
AD_TX_D4_N: U1.K20 (IO_L11N_T1_SRCC_34), U2.E8 (P0_D8/TX_D4_N)
AD_TX_D4_P: U1.K19 (IO_L11P_T1_SRCC_34), U2.D7 (P0_D9/TX_D4_P)
AD_TX_D5_N: U1.J17 (IO_L2N_T0_34), U2.F8 (P0_D10/TX_D5_N)
AD_TX_D5_P: U1.J16 (IO_L2P_T0_34), U2.E7 (P0_D11/TX_D5_P)
AD_TX_FRA_N: U1.R21 (IO_L17N_T2_34), U2.H9 (TX_FRAME_N)
AD_TX_FRA_P: U1.R20 (IO_L17P_T2_34), U2.G9 (TX_FRAME_P)
CEC_G: D10.1 (K), D11.1 (K), IC1.48 (CEC), J13.13 (CEC)
DCCSCL_G: IC1.53 (DDCSCL), J13.15 (SCL), R30.2, U5.2 (D1-)
DCCSDA_G: IC1.54 (DDCSDA), J13.16 (SDA), R31.2, U5.4 (D2+)
DDR_REF: C184.2, C185.1, C186.1, C187.1, C200.2, C201.1, C297.2, C298.2, IC5.H1 (VREFDQ), IC5.M8 (VREFCA), IC7.H1 (VREFDQ), IC7.M8 (VREFCA), IC12.1 (REFOUT), U1.H7 (PS_DDR_VREF0_502), U1.P7 (PS_DDR_VREF1_502)
DN_G: IC3.19 (DM), J12.2 (D-), U9.2 (D1-)
DP_G: IC3.18 (DP), J12.3 (D+), U9.1 (D1+)
ETH_MDC: IC9.7 (MDC), U1.D10 (PS_MIO52_501)
ETH_MDIO: IC9.8 (MDIO), R124.2, U1.C12 (PS_MIO53_501)
ETH_RESET: D5.2 (A), IC9.16 (RESETN), R70.1
ETH_RXD_0: IC9.44 (RXD[0]), U1.E11 (PS_MIO23_501)
ETH_RXD_1: IC9.45 (RXD[1}), U1.B7 (PS_MIO24_501)
ETH_RXD_2: IC9.47 (RXD[2]), U1.F12 (PS_MIO25_501)
ETH_RXD_3: IC9.48 (RXD[3]), U1.A13 (PS_MIO26_501)
ETH_RX_CLK: IC9.46 (RX_CLK), U1.A14 (PS_MIO22_501)
ETH_RX_CTRL: IC9.43 (RX_CTRL), U1.D7 (PS_MIO27_501)
ETH_TXD_0: IC9.50 (TXD[0]), U1.E9 (PS_MIO17_501)
ETH_TXD_1: IC9.51 (TXD[1]), U1.A7 (PS_MIO18_501)
ETH_TXD_2: IC9.54 (TXD[2]), U1.E10 (PS_MIO19_501)
ETH_TXD_3: IC9.55 (TXD[3]), U1.A8 (PS_MIO20_501)
ETH_TX_CLK: IC9.53 (TX_CLK), U1.D6 (PS_MIO16_501)
ETH_TX_CTRL: IC9.56 (TX_CTRL), U1.F11 (PS_MIO21_501)
GND: C1.2, C2.2, C3.2, C4.2, C5.2, C6.2, C7.2, C8.2, C9.2, C10.2, C11.2, C12.2, C13.2, C14.2, C15.2, C16.2, C17.2, C18.2, C19.2, C20.2, C21.2, C22.2, C23.2, C24.2, C25.2, C26.2, C27.2, C28.2, C29.2, C30.2, C31.2, C32.2, C33.2, C34.2, C35.2, C36.2, C37.2, C38.2, C39.2, C40.1, C41.2, C42.2, C43.2, C44.2, C45.2, C46.2, C47.2, C48.2, C49.2, C50.2, C51.2, C52.2, C53.2, C54.2, C55.2, C56.2, C57.2, C58.2, C59.2, C60.2, C61.2, C62.2, C63.2, C64.2, C65.2, C66.2, C69.2, C70.2, C71.2, C74.2, C75.2, C77.2, C78.2, C79.2, C80.2, C81.2, C82.2, C83.2, C84.2, C85.2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
GPIO_33_1: J8.2, U1.V8 (IO_L2P_T0_13)
GPIO_33_2: J8.4, U1.W8 (IO_L2N_T0_13)
GPIO_33_3: J8.8, U1.W11 (IO_L3P_T0_DQS_13)
GPIO_33_4: J8.10, U1.W10 (IO_L3N_T0_DQS_13)
GPIO_33_5: J8.14, U1.V12 (IO_L4P_T0_13)
GPIO_33_6: J8.16, U1.W12 (IO_L4N_T0_13)
GPIO_33_7: J8.20, U1.U12 (IO_L5P_T0_13)
GPIO_33_8: J8.22, U1.U11 (IO_L5N_T0_13)
GPIO_33_9: J8.26, U1.U10 (IO_L6P_T0_13)
GPIO_33_10: J8.28, U1.U9 (IO_L6N_T0_VREF_13)
GPIO_33_11: J8.32, U1.AA12 (IO_L7P_T1_13)
GPIO_33_12: J8.34, U1.AB12 (IO_L7N_T1_13)
GPIO_33_13: J8.38, U1.AA11 (IO_L8P_T1_13)
GPIO_33_14: J8.40, U1.AB11 (IO_L8N_T1_13)
GPIO_33_15: J8.44, U1.AB10 (IO_L9P_T1_DQS_13)
GPIO_33_16: J8.46, U1.AB9 (IO_L9N_T1_DQS_13)
GPIO_33_17: J8.50, U1.Y6 (IO_L13P_T2_MRCC_13)
GPIO_33_18: J8.52, U1.Y5 (IO_L13N_T2_MRCC_13)
GPIO_33_19: J8.56, U1.AA7 (IO_L14P_T2_SRCC_13)
GPIO_33_20: J8.58, U1.AA6 (IO_L14N_T2_SRCC_13)
GPIO_33_21: J8.62, U1.AB2 (IO_L15P_T2_DQS_13)
GPIO_33_22: J8.64, U1.AB1 (IO_L15N_T2_DQS_13)
GPIO_33_23: J8.68, U1.AB5 (IO_L16P_T2_13)
GPIO_33_24: J8.70, U1.AB4 (IO_L16N_T2_13)
GPIO_33_25: J8.74, U1.AB7 (IO_L17P_T2_13)
GPIO_33_26: J8.76, U1.AB6 (IO_L17N_T2_13)
GPIO_33_27: J8.80, U1.Y4 (IO_L18P_T2_13)
GPIO_33_28: J8.82, U1.AA4 (IO_L18N_T2_13)
GPIO_33_29: J8.86, U1.R6 (IO_L19P_T3_13)
GPIO_33_30: J8.88, U1.T6 (IO_L19N_T3_VREF_13)
GPIO_33_31: R119.1, U1.T4 (IO_L20P_T3_13)
GPIO_33_32: R120.1, U1.U4 (IO_L20N_T3_13)
GPIO_33_33: R117.1, U1.V5 (IO_L21P_T3_DQS_13)
GPIO_33_34: R118.1, U1.V4 (IO_L21N_T3_DQS_13)
HD_CLK: IC1.79 (CLK), U1.W18 (IO_L13N_T2_MRCC_33)
HD_D0: IC1.88 (D8), U1.Y13 (IO_L23P_T3_33)
HD_D1: IC1.87 (D9), U1.AA13 (IO_L23N_T3_33)
HD_D2: IC1.86 (D10), U1.AA14 (IO_L22N_T3_33)
HD_D3: IC1.85 (D11), U1.Y14 (IO_L22P_T3_33)
HD_D4: IC1.84 (D12), U1.AB15 (IO_L24N_T3_33)
HD_D5: IC1.83 (D13), U1.AB16 (IO_L18N_T2_33)
HD_D6: IC1.82 (D14), U1.AA16 (IO_L18P_T2_33)
HD_D7: IC1.81 (D15), U1.AB17 (IO_L17N_T2_33)
HD_D8: IC1.80 (D16), U1.AA17 (IO_L17P_T2_33)
HD_D9: IC1.78 (D17), U1.Y15 (IO_L21N_T3_DQS_33)
HD_D10: IC1.74 (D18), U1.W13 (IO_L20N_T3_33)
HD_D11: IC1.73 (D19), U1.W15 (IO_L21P_T3_DQS_33)
HD_D12: IC1.72 (D20), U1.V15 (IO_L19N_T3_VREF_33)
HD_D13: IC1.71 (D21), U1.U17 (IO_L16P_T2_33)
HD_D14: IC1.70 (D22), U1.V14 (IO_L19P_T3_33)
HD_D15: IC1.69 (D23), U1.V13 (IO_L20P_T3_33)
HD_DE: IC1.97 (DE), U1.U16 (IO_L15N_T2_DQS_33)
HD_HSYNC: IC1.98 (HSYNC), U1.V17 (IO_L16N_T2_33)
HD_INT: IC1.45 (INT), R28.2, U1.W16 (IO_L14P_T2_SRCC_33)
HD_SCL: IC1.55 (SCL), R26.2, U1.AA18 (IO_L12N_T1_MRCC_33)
HD_SDA: IC1.56 (SDA), R27.2, U1.Y16 (IO_L14N_T2_SRCC_33)
HD_SPDIF: IC1.10 (SPDIF), U1.U15 (IO_L15P_T2_DQS_33)
HD_SPDIFO: IC1.46 (SPDIF_OUT), U1.Y18 (IO_L12P_T1_MRCC_33)
HD_VSYNC: IC1.2 (VSYNC), U1.W17 (IO_L13P_T2_MRCC_33)
unnamed: C41.1, R21.2
unnamed: C48.1, R22.2
unnamed: C67.2, T1.6
unnamed: C68.2, T1.4
unnamed: C72.2, T3.6
unnamed: C73.2, T3.4
unnamed: C76.1, J4.1, R23.1
unnamed: C246.1, R73.2
unnamed: C250.1, R74.2
unnamed: C253.1, R77.2
unnamed: C317.2, T2.6
unnamed: C318.2, T2.4
unnamed: C322.2, T4.6
unnamed: C323.2, T4.4
unnamed: D2.2, J7.1, L3.2, T1.3, U6.3
unnamed: D3.2, J2.1, T3.3
unnamed: D4.2 (A), IC3.27 (RESETB), R18.1
unnamed: D4.1 (K), R25.1
unnamed: D6.2 (A), R117.2
unnamed: D7.2 (A), R118.2
unnamed: D8.2 (A), R119.2
unnamed: D9.2 (A), R120.2
unnamed: D10.2 (A), R123.2
unnamed: D12.2, J9.1, L9.2, U10.3
unnamed: D13.2, J16.1, T4.3
unnamed: IC1.28 (R_EXT), R29.1
unnamed: IC2.24 (SEL), R7.1
unnamed: IC3.17 (CPEN), IC4.4 (~EN), R20.1
unnamed: C108.1, IC3.22 (VBUS), J10.1, J11.2, J12.1 (VBUS), U9.4 (D2+)
unnamed: C106.1, IC3.12 (VDD15)
unnamed: IC4.1 (OUT), J10.2
unnamed: IC5.L8 (ZQ), R38.1
unnamed: C245.1, IC6.12 (BST1)
unnamed: C248.1, IC6.19 (BST2)
unnamed: C251.1, IC6.39 (BST3)
unnamed: C247.1, IC6.8 (CMP1), R73.1
unnamed: C252.1, IC6.3 (CMP3), R77.1
unnamed: C249.1, IC6.23 (COMP2), R74.1
unnamed: C242#2.1, IC6.7 (FB1), R71.2, R72.1
unnamed: C243.1, IC6.24 (FB2), R75.2, R76.1
unnamed: IC6.4 (FB3), R78.2, R79.1
unnamed: C245.2, IC6.14 (LX1_1), IC6.15 (LX1_2), L4.1
unnamed: C248.2, IC6.16 (LX2_1), IC6.17 (LX2_2), L5.1
unnamed: C251.2, IC6.36 (LX3_1), IC6.37 (LX3_2), L6.1
unnamed: IC6.10 (RLIM1), R82.2
unnamed: IC6.21 (RLIM2), R81.2
unnamed: IC6.1 (RLIM3), R80.2
unnamed: IC6.6 (ROSC), R83.2
unnamed: C259.2, IC6.9 (SS1)
unnamed: C258.2, IC6.22 (SS2)
unnamed: C257.2, IC6.2 (SS3)
unnamed: C260.1, IC6.29 (V3V)
unnamed: C261.1, IC6.28 (V7V)
unnamed: IC7.L8 (ZQ), R37.1
unnamed: IC9.15 (CONFIG), R66.1
unnamed: C233.1, IC9.37 (REGCAP1)
unnamed: C233.2, IC9.41 (REGCAP2)
unnamed: IC9.30 (RSET), R67.1
unnamed: C238.1, IC9.34 (XTAL_IN), Y5.1 (CRYSTAL_1)
unnamed: C239.1, IC9.33 (XTAL_OUT), Y5.3 (CRYSTAL_2)
unnamed: C284.2, IC10.7 (SS)
unnamed: C292.2, IC11.7 (SS)
unnamed: C299.1, IC12.4 (REFIN), R87.2, R89.2
unnamed: C305.1, IC13.4 (BYP)
unnamed: C303.1, C308.1, IC14.5 (VOUT), Y6.4 (VDD)
unnamed: IC15.11 (AS0), IC16.2 (E1)
unnamed: IC15.13 (AS1), IC16.1 (E0)
unnamed: C309.1, IC15.8 (DCAP)
unnamed: C310.1, IC15.7 (VREF)
unnamed: J5.1, R101.2, R102.1
unnamed: C109.1, J11.1
unnamed: C147.1, J13.14 (UTILITY/HEAC+), R32.1
unnamed: J15.11 (MH_1), J15.12 (MH_2), R96.1
unnamed: J17.CD1 (CARD_DETECTION), R127.2
unnamed: L7.1, U7.1 (SW), U7.2 (SW), U7.3 (SW)
unnamed: L8.1, U8.1 (SW), U8.2 (SW), U8.3 (SW)
unnamed: R93.1, S1.1 (COM), U1.C9 (PS_SRST_B_501)
unnamed: R10.2, SW2.2 (B)
unnamed: R9.2, SW3.2 (B)
unnamed: R99.1, SW4.2 (B)
unnamed: R100.2, SW4.1 (C)
unnamed: T2.3, U10.1
unnamed: R4.1, U1.T13 (CFGBVS_0)
unnamed: R101.1, U1.K16 (IO_L3P_T0_DQS_PUDC_B_34)
unnamed: R97.2, U1.E14 (PS_MIO40_501)
unnamed: C302.1, FB15.2, U1.K12 (GNDADC_0), U1.L11 (VP_0), U1.L12 (VREFN_0), U1.M11 (VREFP_0), U1.M12 (VN_0)
unnamed: C302.2, FB14.1, U1.K11 (VCCADC_0)
unnamed: R21.1, U2.G2 (RX_VCO_LDO_OUT), U2.G3 (VDDA1P1_RX_VCO)
unnamed: R22.1, U2.A11 (VDDA1P1_TX_VCO), U2.B11 (TX_VCO_LDO_OUT)
unnamed: C40.2, TP4.1, U2.B3 (AUXDAC1)
unnamed: R16.2, U2.L4 (RBIAS)
unnamed: C76.2, U2.M12 (XTALN), Y6.3 (OUTPUT)
unnamed: R84.2, R85.1, U7.5 (FB)
unnamed: C262.2, U7.9 (SS/TR)
unnamed: R125.2, R126.1, U8.5 (FB)
unnamed: C264.2, U8.9 (SS/TR)
unnamed: R121.2, Y1.3 (OUT)
unnamed: R122.1, Y1.1 (~ST)
unnamed: R92.1, Y2.3 (OUT)
unnamed: R17.2, Y2.1 (~ST)
unnamed: R24.1, Y3.1 (~ST)
unnamed: R5.2, Y4.1 (~ST)
OTG_CLK: IC3.26 (CLOCK), U1.A9 (PS_MIO36_501)
OTG_D0: IC3.3 (DATA0), U1.C7 (PS_MIO32_501)
OTG_D1: IC3.4 (DATA1), U1.G13 (PS_MIO33_501)
OTG_D2: IC3.5 (DATA2), U1.B12 (PS_MIO34_501)
OTG_D3: IC3.6 (DATA3), U1.F14 (PS_MIO35_501)
OTG_D4: IC3.7 (DATA4), U1.A12 (PS_MIO28_501)
OTG_D5: IC3.9 (DATA5), U1.B14 (PS_MIO37_501)
OTG_D6: IC3.10 (DATA6), U1.F13 (PS_MIO38_501)
OTG_D7: IC3.13 (DATA7), U1.C13 (PS_MIO39_501)
OTG_DIR: IC3.31 (DIR), U1.E8 (PS_MIO29_501)
OTG_NXT: IC3.2 (NXT), U1.F9 (PS_MIO31_501)
OTG_OC: IC4.3 (~OC), R19.2, U1.L16 (IO_L3N_T0_DQS_34)
OTG_RCLK: C111.1, IC3.1 (REFCLK), Y3.3 (OUT)
OTG_RST: R25.2, U1.G17 (IO_L6P_T0_35)
OTG_STP: IC3.29 (STP), U1.A11 (PS_MIO30_501)
PS_POR_B: D5.1 (K), IC12.5 (PGOOD), R90.2, U1.B5 (PS_POR_B_500)
SD_CD: R98.1, R127.1, U1.B10 (PS_MIO47_501)
SD_CLK: IC2.9 (CLKA), R97.1
SD_CMD: IC2.4 (CMDA), U1.C8 (PS_MIO41_501)
SD_D0: IC2.6 (DAT0A), U1.D8 (PS_MIO42_501)
SD_D1: IC2.7 (DAT1A), U1.B11 (PS_MIO43_501)
SD_D2: IC2.1 (DAT2A), U1.E13 (PS_MIO44_501)
SD_D3: IC2.3 (DAT3A), U1.B9 (PS_MIO45_501)
SD_WP: SW4.3 (A), U1.D12 (PS_MIO46_501)
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
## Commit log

2026-05-05 Add README for Zynq-7020 SDR Carrier Board
    Add detailed project information for Zynq-7020 SDR Carrier Board including specifications, hardware design, and software tools.
2026-05-05 Rename project from Zynq-7020 SDR to PeriR
2026-05-05 changed folder name
